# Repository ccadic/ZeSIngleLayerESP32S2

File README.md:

# ZeSIngleLayerESP32S2
Single Layer ESP32S2 USB dongle to make it with a CNC
SVG files included

All R and C are 1206 SMD components.

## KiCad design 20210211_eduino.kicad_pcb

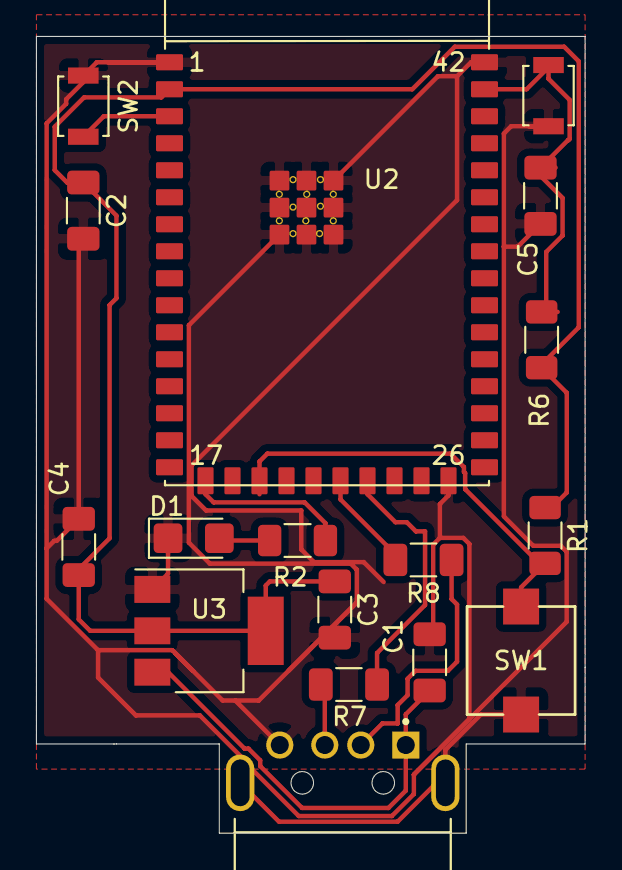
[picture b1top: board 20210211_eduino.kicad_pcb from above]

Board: 2 copper layers, 30.5 x 44.3 mm, 17 parts (0 on the bottom side), 12 nets.

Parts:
C1, C2: 10u; C_1206_3216Metric_Pad1.33x1.80mm_HandSolder
C3, C4, C5: 100n; C_1206_3216Metric_Pad1.33x1.80mm_HandSolder
D1: LED_Small; LED_1206_3216Metric_Castellated
J1: 48037-0001; MOLEX_48037-0001
R1, R6: 10k; R_1206_3216Metric_Pad1.30x1.75mm_HandSolder
R2: 330R; R_1206_3216Metric_Pad1.30x1.75mm_HandSolder
R7, R8: 22R; C_1206_3216Metric_Pad1.33x1.80mm_HandSolder
SW1: SW_Push_45deg; SW_TP1003
SW2, SW3: esp32Rst; SW_SPST_B3U-1000P
U2: ESP32-S2-WROOM; esp32-s2-wrooom
U3: AP1117-33; SOT-223-3_TabPin2

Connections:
+3V3: C2.1, C3.1, C4.1, R1.1, R6.1, U2.2, U3.2
/BOOT: SW2.2, U2.3
/BOUTON2: R1.2, SW1.1, U2.19
/EN: C5.1, R6.2, SW3.2, U2.41
/ESP_D+: J1.3, R7.1
/ESP_D-: J1.2, R8.1
/TFTDC: R2.1, U2.17
GND: C1.2, C2.2, C3.2, C4.2, C5.2, D1.1, J1.4, J1.S1, J1.S2, SW1.2, SW2.1, SW3.1, U2.1, U2.26, U2.42, U2.43, U3.1
unnamed: D1.2, R2.2
unnamed: R7.2, U2.23
unnamed: R8.2, U2.22
VBUS: C1.1, J1.1, U3.3
